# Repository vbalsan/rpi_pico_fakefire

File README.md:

# rpi_pico_fakefire

The electric fireplace project.

Main goal is to have this :

But with flickering, and sound, and little bonus like color control...
Idea came after landlord decided that we could not use our fireplace anymore, and didn't want to pay 400-500 bucks for an electric one.

## **How to ?**
The trick is to use foam (the kind you can find at reno store for filling cracks and holes) with lights, of course since just simple Christmas lights don't twinkle, we need to use a microcontroller with leds.

After several tests, I abandonned the idea of leds with PWM, for a led strip, much better, but the ws2812/ws2811 needs special timings.
Used ATtiny85 at the beginning since I had plenty, but the low-power 10MHz versions cannot manage the 800 or 400kHz ws2811 chips plus the calculation for the lights.

As I found, a raspberry pico is much better for the project, the PIOs can decipher IR reception without stopping the stream (a complete IR frame is around 40ms) , and I could write a PIO-assembly program to manage the lights within the main C file.
Could have gone with the rp2040 only, but for 4$...

## **What is there in the end ?**
Final board contains :
- a 12V / 5V converter, switching DC-DC
- a MOSFET to control 12V supply to the strip
- NAND gate for 3.3V to 5V conversion (could have done with diode)
- a DFPlayer for the sound
- a PAM8403 for amplification (not really necessary for one 4 Ohm speaker)
- TSOP1838B IR receiver
- a raspberry pico for all the logic
- a 4 Ohm speaker
- several old 5mm leds and through hole resistor for a retro look

## **Analysis for the signal controlling the ws2811 :**

This gave me the occasion to create libraries for the IR receiver (TSOP1838B) and the ws2811.

## **The PCB :**
First prototype was on a... prototype board, but decided to go real PCB with Kicad and JLCPCB, result :

PCB in 3D on Kicad

PCB received

PCB almost fully populated

## **What now ?**
So far, project is continuing... There are issues on IR reception, probably using 3 resistors to decrease the voltage from 5V to 3.3 for GPIO was not a good idea.
Need to make some tests as I could not find the input impedance of the pico GPIO.

## **Pro/cons**

- I've put 16V capacitor for the 12V supply, it's bad, but it was what I had in my drawer
- Forgot to put a UART/serial port, quite a mess to debug even if I could use the SWD
- Didn't add filtering for the sound, not specialist in this, right now the cracking wood sound is more like frying oil.

## **Mapping buttons : **

on off (top)                    menu
BA45FF00                        B847FF00

Test            +               return
BB44FF00        BF40FF00        BC43FF00

<<              play            >>
F807FF00        EA15FF00        F609FF00

0               -               C
E916FF00        E619FF00        F20DFF00

1               2               3
F30CFF00        E718FF00        A15EFF00

4               5               6
F708FF00        E31CFF00        A55AFF00

7               8               9
BD42FF00        AD52FF00        B54AFF00

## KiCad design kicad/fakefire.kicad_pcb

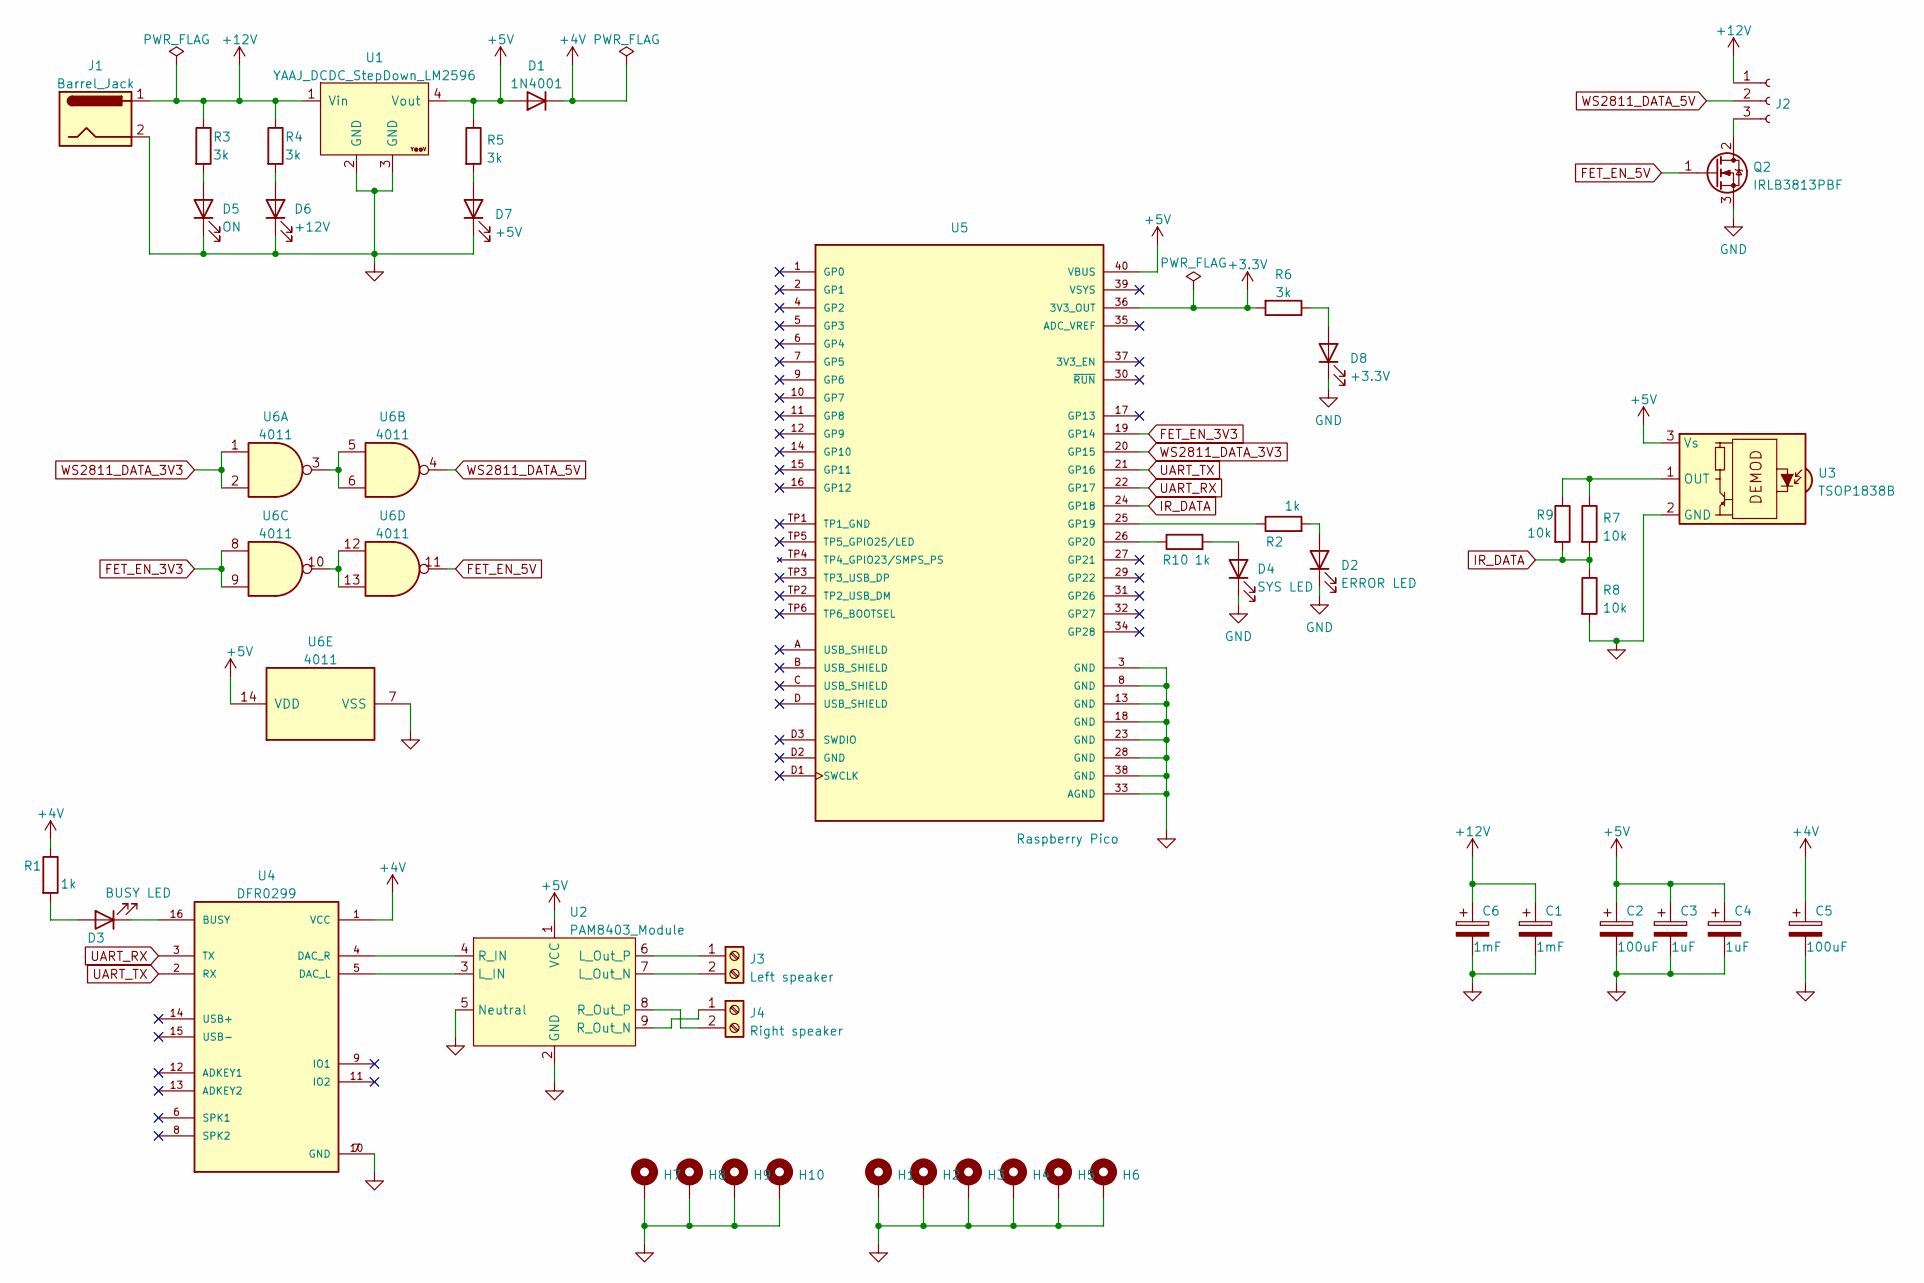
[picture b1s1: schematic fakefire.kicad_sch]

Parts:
C1, C6: 1mF; CP_Radial_D10.0mm_P5.00mm
C2, C5: 100uF; CP_Radial_D5.0mm_P2.00mm
C3, C4: 1uF; CP_Radial_D5.0mm_P2.00mm
D1: 1N4001; D_DO-41_SOD81_P10.16mm_Horizontal
D2: ERROR LED; LED_D5.0mm
D3: BUSY LED; LED_D5.0mm
D4: SYS LED; LED_D5.0mm
D5: ON; LED_D5.0mm
D6: +12V; LED_D5.0mm
D7: +5V; LED_D5.0mm
D8: +3.3V; LED_D5.0mm
H1, H2, H3, H4, H5, H6: MountingHole_Pad; MountingHole_3.5mm_Pad_Via
H7, H8, H9, H10: MountingHole_Pad; MountingHole_3.7mm_Pad_Via
J1: Barrel_Jack; BarrelJack_Horizontal
J2: Conn_01x03_Female; SolderWire-1sqmm_1x03_P5.4mm_D1.4mm_OD2.7mm
J3: Left speaker; TerminalBlock_bornier-2_P5.08mm
J4: Right speaker; TerminalBlock_bornier-2_P5.08mm
Q2: IRLB3813PBF; TO-220-3_Vertical
R1, R2, R10: 1k; R_Axial_DIN0207_L6.3mm_D2.5mm_P10.16mm_Horizontal
R3, R4, R5, R6: 3k; R_Axial_DIN0207_L6.3mm_D2.5mm_P10.16mm_Horizontal
R7, R8, R9: 10k; R_Axial_DIN0207_L6.3mm_D2.5mm_P10.16mm_Horizontal
U1: YAAJ_DCDC_StepDown_LM2596
U2: PAM8403_Module
U3: TSOP1838B; Vishay_MINICAST-3Pin
U4: DFR0299; MODULE_DFR0299
U5: Raspberry Pico; Pico; PARTREV 1.6
U6: 4011; DIP-14_W7.62mm_Socket

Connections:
+3.3V: R6.2, U5.36 (3V3_OUT)
+4V: C5.1, D1.1 (K), R1.1, U4.1 (VCC)
+5V: C2.1, C3.1, C4.1, D1.2 (A), R5.1, U1.4 (Vout), U2.1 (VCC), U3.3 (Vs), U5.40 (VBUS), U6.14 (VDD)
+12V: C1.1, C6.1, J1.1, J2.1, R3.1, R4.1, U1.1 (Vin)
FET_EN_3V3: U5.19 (GP14), U6.8, U6.9
FET_EN_5V: Q2.1 (G), U6.11
GND: C1.2, C2.2, C3.2, C4.2, C5.2, C6.2, D2.1 (K), D4.1 (K), D5.1 (K), D6.1 (K), D7.1 (K), D8.1 (K), H1.1, H2.1, H3.1, H4.1, H5.1, H6.1, H7.1, H8.1, H9.1, H10.1, J1.2, Q2.3 (S), R8.2, U1.2 (GND), U1.3 (GND), U2.2 (GND), U2.5 (Neutral), U3.2 (GND), U4.7 (GND), U4.10 (GND), U5.3 (GND), U5.8 (GND), U5.13 (GND), U5.18 (GND), U5.23 (GND), U5.28 (GND), U5.33 (AGND), U5.38 (GND), U6.7 (VSS)
IR_DATA: R7.2, R8.1, R9.2, U5.24 (GP18)
unnamed: D2.2 (A), R2.2
unnamed: D3.1 (K), U4.16 (BUSY)
unnamed: D3.2 (A), R1.2
unnamed: D4.2 (A), R10.2
unnamed: D5.2 (A), R3.2
unnamed: D6.2 (A), R4.2
unnamed: D7.2 (A), R5.2
unnamed: D8.2 (A), R6.1
unnamed: J2.3, Q2.2 (D)
unnamed: J3.1, U2.6 (L_Out_P)
unnamed: J3.2, U2.7 (L_Out_N)
unnamed: J4.1, U2.9 (R_Out_N)
unnamed: J4.2, U2.8 (R_Out_P)
unnamed: R2.1, U5.25 (GP19)
unnamed: R7.1, R9.1, U3.1 (OUT)
unnamed: U2.3 (L_IN), U4.5 (DAC_L)
unnamed: U2.4 (R_IN), U4.4 (DAC_R)
unnamed: R10.1, U5.26 (GP20)
unnamed: U6.3, U6.5, U6.6
unnamed: U6.10, U6.12, U6.13
UART_RX: U4.3 (TX), U5.22 (GP17)
UART_TX: U4.2 (RX), U5.21 (GP16)
WS2811_DATA_3V3: U5.20 (GP15), U6.1, U6.2
WS2811_DATA_5V: J2.2, U6.4

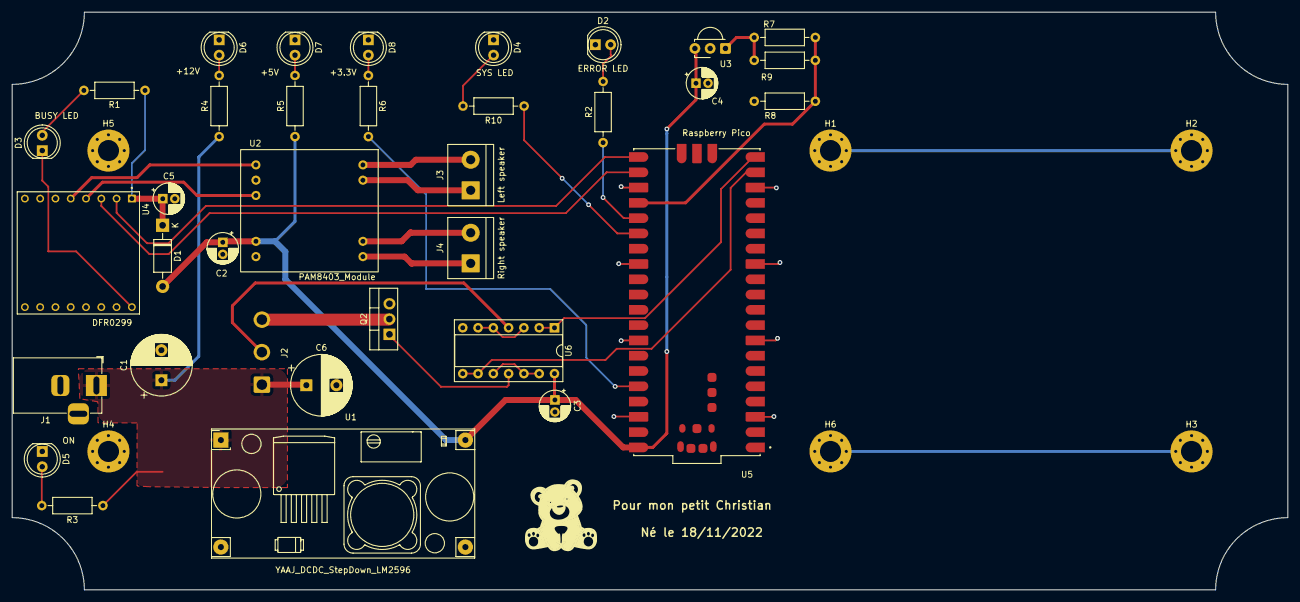
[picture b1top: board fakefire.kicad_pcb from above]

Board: 2 copper layers, 212.0 x 96.0 mm, 41 parts (0 on the bottom side), 32 nets.

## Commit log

2022-09-09 led ws2811 functional with PIO
2022-09-10 IR remote operational
2022-09-29 reorganisation
2022-09-29 all 3 libs separated
2022-11-05 all leds working + better interface for libraries
2022-11-07 audio working
2023-01-27 folder
2023-01-27 kicad pcb
2023-01-27 img folder
2023-02-02 update kicad files, added more infos, comments
2023-02-02 Added debug functions, now it starts from power on
